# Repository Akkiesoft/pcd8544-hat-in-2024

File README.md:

# 令和6年最新版 PCD8544 HAT

PCD8544 (a.k.a. Nokia5110) ディスプレイをRaspberry Piで使用するための拡張ボードです。84x48しかないレトロなモノクロLCDでグラフィック表示を楽しんでみませんか？

## 特徴

* Raspberry Piの標準的なSPIピンに配線
* GPIOで制御可能なバックライト
* uHAT規格のマウントホールを用意 (ボードサイズはuHATよりももう少し大きいです)
* 4つのボタンを配置

## サンプルスクリプト

サンプルスクリプトはCircuitPythonで記述されています。

* pcd8544_demo.py
    * 基本的なデモスクリプトです
    * 左上のボタンを押すとバックライトのオン・オフ切り替え
    * 左下のボタンを押すとグラフ表示ライブラリのサンプルを表示
    * 右上と右下のボタンを押すと画像データを表示

## ライブラリ

いずれもpcd8544_demo.pyで使用例が確認できます。

* draw_img
    * フレームバッファ形式に合わせた画像の配列データを描画します
* draw_graph
    * グラフを描画します

## ユーティリティスクリプト

* img_convert.py
    * 84x48の画像を、draw_imgライブラリで描画可能な配列形式に変換します

## 基板データ

TBD

## 部品リスト

* 1x BSS138
    * https://akizukidenshi.com/catalog/g/g111627/
* 1x 0.1uF 積層セラミックコンデンサー
    * https://akizukidenshi.com/catalog/g/g117576/
* 1x 10KΩ表面実装抵抗 (2012/0805サイズ)
* 4x 330Ω表面実装抵抗 (2012/0805サイズ)
    * LED用。LEDに合わせて適宜変更してください
* 4x 表面実装LED (2012/0805サイズ)
    * https://akizukidenshi.com/catalog/g/g106423/
    * https://akizukidenshi.com/catalog/g/g106424/
    * https://akizukidenshi.com/catalog/g/g106425/
* 4x 表面実装ボタン (3mm * 4mm * 2.5mm)
    * https://aliexpress.com/item/1005004888773791.html
* PCD8544
    * https://aliexpress.com/item/1005005594822679.html

## Used libraries and footprint

* [KiCad footprint for Nokia 5110 LCD](https://hackaday.io/page/3427-kicad-footprint-for-nokia-5110-lcd)
    * by sgreg, MIT License

## License

令和6年最新版 PCD8544 HAT (PCD8544 HAT in 2024)

2024 @Akkiesoft, MIT License

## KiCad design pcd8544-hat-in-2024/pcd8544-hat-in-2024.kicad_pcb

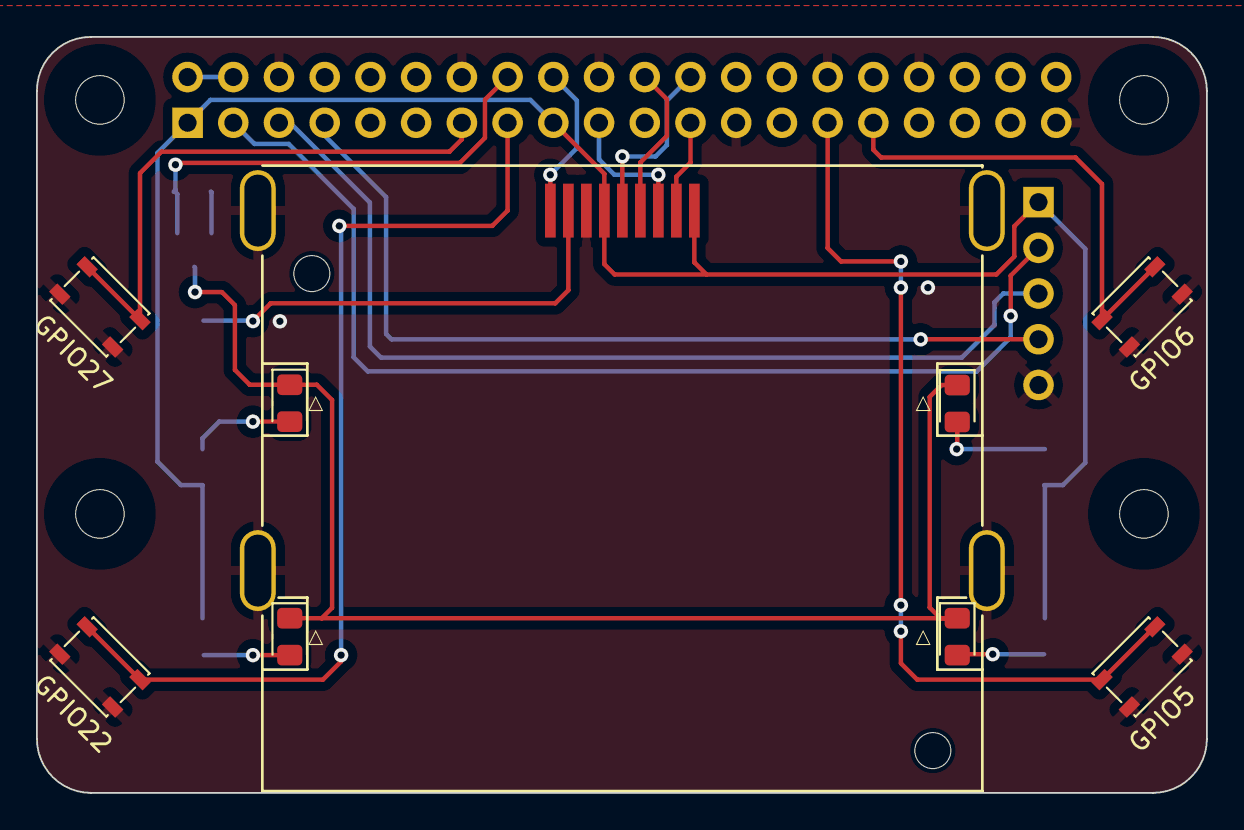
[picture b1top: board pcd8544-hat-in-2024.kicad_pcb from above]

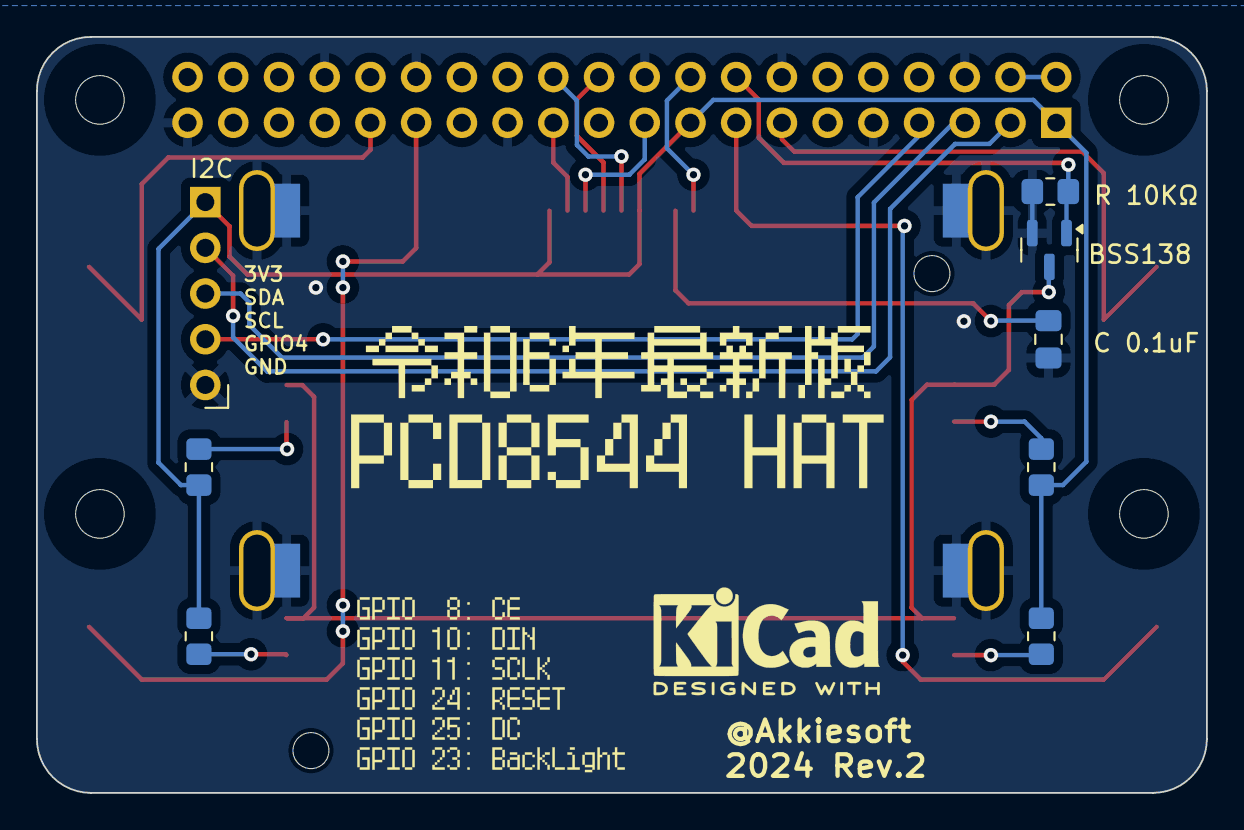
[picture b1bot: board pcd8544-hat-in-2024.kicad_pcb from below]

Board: 2 copper layers, 65.0 x 42.0 mm, 22 parts (9 on the bottom side), 22 nets.

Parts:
C1: C 0.1uF; C_0805_2012Metric_Pad1.18x1.45mm_HandSolder
D1, D2, D3, D4: LED; LED_0805_2012Metric_Pad1.15x1.40mm_HandSolder
GPIO5, GPIO6, GPIO22, GPIO27: SW_Push; SW_SPST_PTS810
H1, H2, H3, H4: MountingHole; MountingHole_2.7mm_M2.5_uHAT_RPi
J1: Raspberry_Pi_2_3; PinSocket_2x20_P2.54mm_Vertical_Centered_Anchor
J2: Conn_01x05_Socket; PinHeader_1x05_P2.54mm_Horizontal
Q2: BSS138; SOT-23
R1, R2, R3, R4: R; R_0805_2012Metric_Pad1.20x1.40mm_HandSolder
R 10KΩ: R; R_0805_2012Metric_Pad1.20x1.40mm_HandSolder
U1: Nokia_5110_LCD; Nokia_5110-3310_LCD

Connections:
+3V3: J1.1 (3V3), J1.17 (3V3), J2.5, R1.2, R2.2, R3.2, R4.2, U1.4 (OSC), U1.9 (VCC)
+5V: J1.2 (5V), J1.4 (5V)
BTN_1: GPIO22.1, J1.15 (GPIO22)
BTN_2: GPIO27.1, J1.13 (GPIO27)
BTN_3: GPIO5.1, J1.29 (GCLK1/GPIO5)
BTN_4: GPIO6.1, J1.31 (GCLK2/GPIO6)
GND: C1.2, GPIO5.2, GPIO6.2, GPIO22.2, GPIO27.2, J1.6 (GND), J1.9 (GND), J1.14 (GND), J1.20 (GND), J1.25 (GND), J1.30 (GND), J1.34 (GND), J1.39 (GND), J2.1, Q2.2 (S), R 10KΩ.2, U1.3 (GND)
unnamed: D1.2 (A), R1.1
unnamed: D1.1 (K), D2.1 (K), D3.1 (K), D4.1 (K), Q2.3 (D)
unnamed: D2.2 (A), R2.1
unnamed: D3.2 (A), R3.1
unnamed: D4.2 (A), R4.1
unnamed: J1.7 (GCLK0/GPIO4), J2.2
unnamed: J1.16 (GPIO23), Q2.1 (G), R 10KΩ.1
unnamed: J1.18 (GPIO24), U1.1 (~RST)
unnamed: J1.22 (GPIO25), U1.6 (D/~C)
unnamed: J1.19 (MOSI0/GPIO10), U1.7 (SDIN)
unnamed: J1.23 (SCLK0/GPIO11), U1.8 (SCLK)
unnamed: J1.5 (SCL/GPIO3), J2.3
unnamed: J1.3 (SDA/GPIO2), J2.4
unnamed: J1.24 (~CE0/GPIO8), U1.5 (~SCE)
unnamed: C1.1, U1.2 (VOUT)

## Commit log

2024-10-24 init
2024-10-31 add kicad data and garber data
2024-10-31 add example to using graph
2024-11-10 added variable to select boards
2024-11-10 [co2] add cleanup codes for rpi
2024-11-10 define int_pin in config
2024-11-10 add ds18b20 sample
2024-11-10 [pcd8544_demo] add sleep into main loop
2024-12-01 add example to control display directly
2025-01-03 load ds18b20 module for pico in the if statement
2025-01-03 add example/graph_random.py
